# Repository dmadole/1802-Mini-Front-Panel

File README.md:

# 1802-Mini-Front-Panel
This is the front panel card for the [1802/Mini](https://github.com/dmadole/1802-Mini) system. It supports the following features:

* Supports two, four, or six TIL311 hexadecimal displays
* Left sockets selectable for either LSB or MSB of address
* Toggle switch input to load memory with CDP1802 processor
* Displays and toggle input fully decoded on I/O port 4
* Can separately disable display or toggle I/O ability
* Input switch selectable to EF3 or E4 (or neither)
* Supports LOAD (CDP1802 only), RUN, WAIT, and RESET modes
* In WAIT mode can single-step one machine cycle at a time
* Supports either push button or toggle switch for INPUT
* Stackable to processor card without blocking status LEDs
* Highly annotated silkscreen documents settings and pins

Gerber files for the PCBs and PDF schematics can be found in [Releases](https://github.com/dmadole/1802-Mini-Front-Panel/releases).

BOMS and any applicable errata or other notes can be found in [notes](https://github.com/dmadole/1802-Mini-Front-Panel/tree/main/notes).

For availability of kits and bare PCBs please see http://madole.net/1802/mini/kits

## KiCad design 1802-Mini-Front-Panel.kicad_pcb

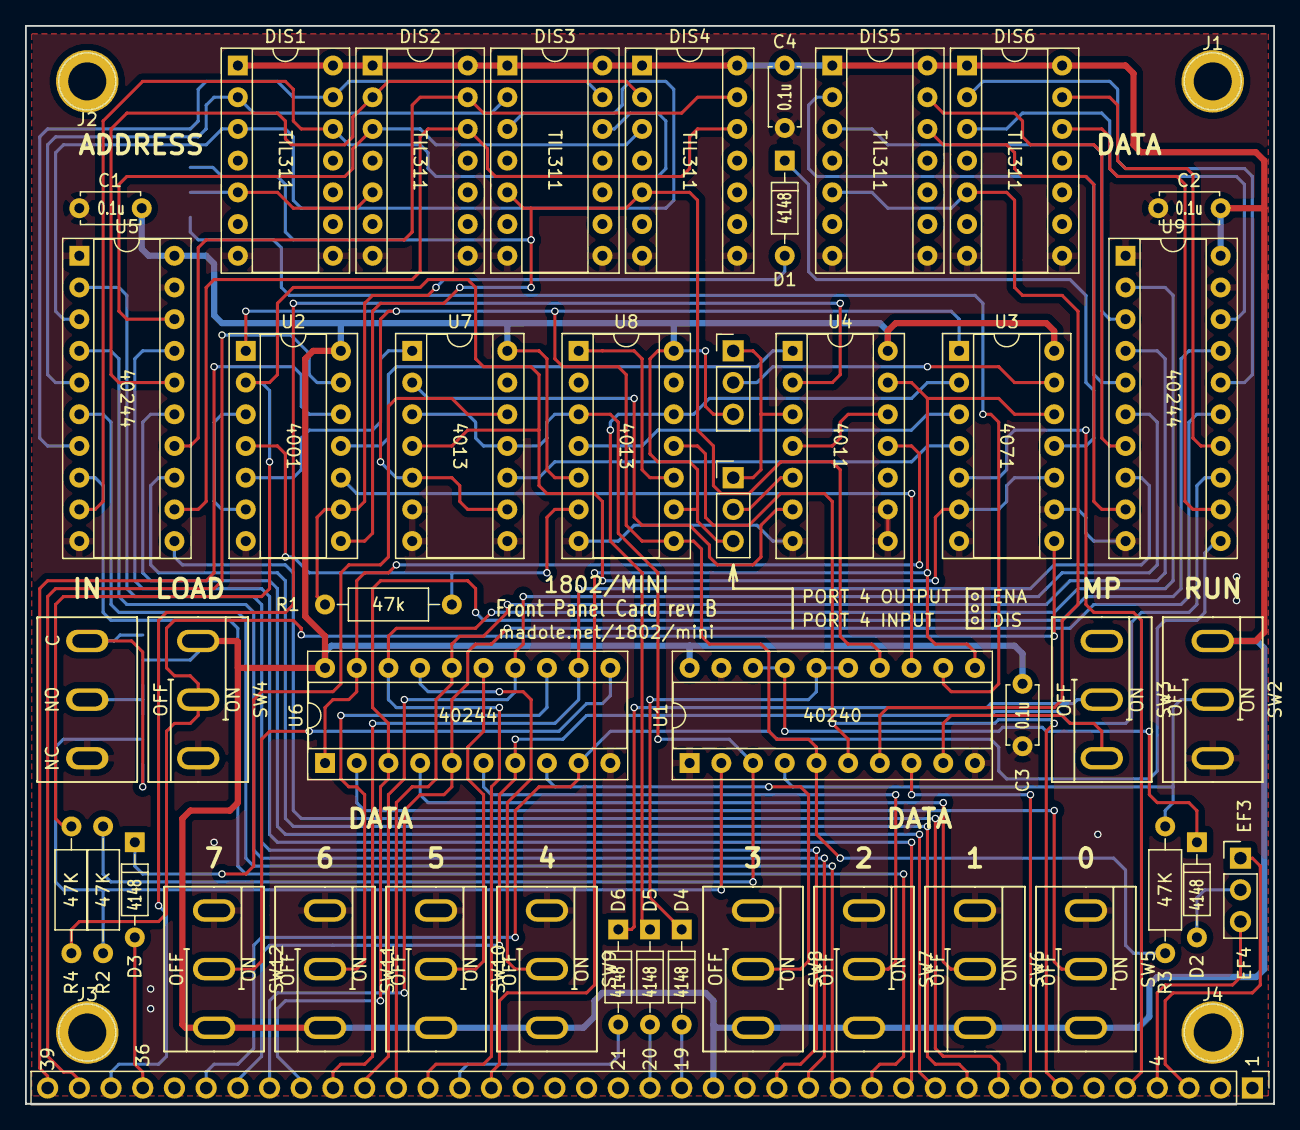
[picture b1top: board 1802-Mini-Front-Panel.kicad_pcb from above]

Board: 2 copper layers, 100.0 x 86.4 mm, 52 parts (0 on the bottom side), 90 nets.

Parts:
C1, C2, C3, C4: 0.1u; C_Disc_D4.7mm_W2.5mm_P5.00mm
D1, D2, D3, D4, D5, D6: 1N4148; D_DO-35_SOD27_P7.62mm_Horizontal
DIS1, DIS2, DIS3, DIS4, DIS5, DIS6: TIL311; DIP-14_W7.62mm_Socket
J1, J2, J3, J4: Mount; 1pin
J5: Expansion; Pin_Header_Straight_1x39_Pitch2.54mm
JP1: Button_Toggle_2; SolderJumper-3_P2.0mm_Open_TrianglePad1.0x1.5mm_NumberLabels
JP2: Button_Toggle_1; SolderJumper-3_P2.0mm_Open_TrianglePad1.0x1.5mm_NumberLabels
JP3: IN_EF; Pin_Header_Straight_1x03_Pitch2.54mm
JP4: MA_HI_LO; SolderJumper-3_P2.0mm_Open_TrianglePad1.0x1.5mm_NumberLabels
JP5: OUTPUT; Pin_Header_Straight_1x03_Pitch2.54mm
JP6: INPUT; Pin_Header_Straight_1x03_Pitch2.54mm
R1, R2, R3, R4: 47k; R_Axial_DIN0207_L6.3mm_D2.5mm_P10.16mm_Horizontal
SW1: IN; SPDT_PUSH
SW2: RUN; SPDT_SWITCH
SW3: MP; SPDT_SWITCH
SW4: LOAD; SPDT_SWITCH
SW5: IN0; SPDT_SWITCH
SW6: IN1; SPDT_SWITCH
SW7: IN2; SPDT_SWITCH
SW8: IN3; SPDT_SWITCH
SW9: IN4; SPDT_SWITCH
SW10: IN5; SPDT_SWITCH
SW11: IN6; SPDT_SWITCH
SW12: IN7; SPDT_SWITCH
U1: 40240; DIP-20_W7.62mm_Socket
U2: 4001; DIP-14_W7.62mm_Socket
U3: 4071; DIP-14_W7.62mm_Socket
U4: 4011; DIP-14_W7.62mm_Socket
U5, U6, U9: CD40244; DIP-20_W7.62mm_Socket
U7, U8: 4013; DIP-14_W7.62mm_Socket

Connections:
/BUS0: J5.27, U6.18, U9.2
/BUS1: J5.28, U6.16, U9.4
/BUS2: J5.29, U6.14, U9.6
/BUS3: J5.30, U6.12, U9.8
/BUS4: J5.31, U6.3, U9.17
/BUS5: J5.32, U6.5, U9.15
/BUS6: J5.33, U6.7, U9.13
/BUS7: J5.34, U6.9, U9.11
/MA0: J5.16, U5.2
/MA1: J5.15, U5.4
/MA2: J5.14, U5.6
/MA3: J5.13, U5.8
/MA4: J5.12, U5.17
/MA5: J5.11, U5.15
/MA6: J5.10, U5.13
/MA7: J5.9, U5.11
DMA_IN: D3.2, J5.36
EF3: J5.3, JP3.1
EF4: J5.4, JP3.3
GND: C1.2, C2.2, C3.2, C4.2, DIS1.7, DIS1.8, DIS2.7, DIS2.8, DIS3.7, DIS3.8, DIS4.7, DIS4.8, DIS5.7, DIS5.8, DIS6.7, DIS6.8, J5.17, SW1.3, SW2.3, SW4.3, SW5.1, SW6.1, SW7.1, SW8.1, SW9.1, SW10.1, SW11.1, SW12.1, U1.1, U1.10, U1.19, U2.7, U3.7, U3.9, U4.7, U4.8, U4.9, U5.1, U5.10, U5.19, U6.10, U7.6, U7.7, U7.8, U8.7, U9.1, U9.10, U9.19
MEN: D6.2, J5.26
MRD: J5.25, U1.11, U3.12, U4.13
N0: J5.39, U2.12
N1: J5.38, U2.13
N2: J5.37, U4.2
unnamed: D1.1, U3.11
unnamed: D1.2, R1.2, U2.9
unnamed: D2.1, U1.17, U1.18
unnamed: D2.2, JP3.2
unnamed: D3.1, U7.12
unnamed: D4.1, U1.15, U1.16
unnamed: D5.1, U3.2, U8.12
unnamed: D6.1, SW3.2
unnamed: DIS1.2, DIS3.2, U5.5
unnamed: DIS1.3, DIS3.3, U5.3
unnamed: DIS1.5, DIS2.5, JP4.2
unnamed: DIS1.12, DIS3.12, U5.9
unnamed: DIS1.13, DIS3.13, U5.7
unnamed: DIS2.2, DIS4.2, U5.16
unnamed: DIS2.3, DIS4.3, U5.18
unnamed: DIS2.12, DIS4.12, U5.12
unnamed: DIS2.13, DIS4.13, U5.14
unnamed: DIS5.2, U9.5
unnamed: DIS5.3, U9.3
unnamed: DIS5.5, DIS6.5, U1.7
unnamed: DIS5.12, U9.9
unnamed: DIS5.13, U9.7
unnamed: DIS6.2, U9.16
unnamed: DIS6.3, U9.18
unnamed: DIS6.12, U9.12
unnamed: DIS6.13, U9.14
unnamed: JP1.1, JP2.3, SW1.2
unnamed: JP1.3, JP2.1, SW1.1
unnamed: JP2.2, R2.1, U1.2
unnamed: JP4.1, U1.12
unnamed: JP5.1, JP6.1, U4.3
unnamed: JP5.2, U3.13
unnamed: JP6.2, U4.5
unnamed: R2.2, U1.3, U7.3, U7.11, U8.3
unnamed: R3.1, SW2.2, U1.4
unnamed: R3.2, U1.5, U2.1, U3.1, U7.5, U7.9, U8.8
unnamed: R4.1, SW4.2, U3.8
unnamed: R4.2, U2.2, U3.6, U3.10, U7.4
unnamed: SW3.3, U1.9
unnamed: SW5.2, U6.2
unnamed: SW6.2, U6.4
unnamed: SW7.2, U6.6
unnamed: SW8.2, U6.8
unnamed: SW9.2, U6.17
unnamed: SW10.2, U6.15
unnamed: SW11.2, U6.13
unnamed: SW12.2, U6.11
unnamed: U2.3, U2.6
unnamed: U2.5, U7.1
unnamed: U2.11, U4.1
unnamed: U3.3, U8.4
unnamed: U3.4, U7.10
unnamed: U4.4, U4.12
unnamed: U8.1, U8.10
READ: U4.11, U6.1, U6.19
SC1: J5.5, U3.5
STROBE: U1.13, U2.10
TPA: J5.8, U1.8
TPB: J5.7, U1.6, U8.11
VCC: C1.1, C2.1, C3.1, C4.1, DIS1.1, DIS1.14, DIS2.1, DIS2.14, DIS3.1, DIS3.14, DIS4.1, DIS4.14, DIS5.1, DIS5.14, DIS6.1, DIS6.14, J5.18, JP1.2, JP5.3, JP6.3, SW2.1, SW4.1, SW5.3, SW6.3, SW7.3, SW8.3, SW9.3, SW10.3, SW11.3, SW12.3, U1.20, U2.14, U3.14, U4.14, U5.20, U6.20, U7.14, U8.5, U8.9, U8.14, U9.20
~CLEAR: D4.2, J5.19
~LOAD: U4.6, U7.2
~LOADSTEP: R1.1, U2.4, U8.6
~TPB: DIS3.5, DIS4.5, JP4.3, U1.14, U2.8
~WAIT: D5.2, J5.20

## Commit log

2021-06-23 Add files via upload
    Add BOM
2021-06-23 Add BOM
2021-06-27 Added notes and references to BOM
2021-06-28 Correct mfr part no of single row header
